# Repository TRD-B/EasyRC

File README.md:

# EasyRC - open-source RC platform

Description
---
EasyRC is an easy-to-build platform for creating your own remote-controlled vehicle. The platform includes CAD files for printing an affordable 1:16 scale car as well as a small remote control. Further, it includes the project and production files for the printed circuit boards that are needed to power these devices. Last but not least, it lists all required components in a bill of materials and comes with a complete instruction manual that shows how to print, solder, assemble, program, and adjust everything for running the car. The legacy folder contains data and information from previous revisions of the project.

The idea of this platform is to serve as a starting point for people who are interested in DIY hobby electronics as well as 3D printing, but were reluctant so far due to the initial burdens that are associated with the complexity of these topics. Hence, EasyRC offers a simple start for beginners, but due to its open-source character, it offers full freedom to tweak, redesign, and reprogram all parts of the project.

The 1:16 scale vehicle is designed for indoor use (for the sake of simplicity, it does not encompass suspension) and can be safely operated by kids (maximum speed is 10 km/h but can be set lower within the software). Hence, the project is also a great gift for kids who want to dive into engineering and programming topics, or start with driving a selfmade remote-controlled car and look behind the scenes once they're getting older.

The manual is available in English and German.

Specifications
---
Vehicle:
- Size: 282x125x95 mm³ (LxWxH)
- Scale: 1:16
- Weight: approx. 1 kg (including batteries)
- Microcontroller: ESP32-C3
- Wireless communication: 2.4 GHz (ESP-NOW protocol)
- Motor driver: Pololu DRV8876 (QFN)
- Drive motor: JGA25-370 Brushed DC motor with gearbox (12 V, 1000 U/min)
- Speed: max. 10 km/h
- Steering servo: MG90S metal-gear micro servo
- Power supply: 3x 18650 Li-Ion battery (11.1 V)
- Power consumption: approx. 0.8 W (idle); approx. 3-6 W (driving)

Remote control:
- Size: 80x40x41 mm³ (LxWxH)
- Weight: approx. 125 g (including battery)
- Microcontroller: ESP32-C3
- Wireless communication: 2.4 GHz (ESP-NOW protocol)
- Joystick: Alps 10k (Playstation 4 model)
- Power supply: 1x 18650 Li-Ion battery (3.7 V)
- Power consumption: approx. 0.5 W

Safety information:
---
- Voltage levels are 12 V or less (harmless for humans)
-	Battery connectors are reverse polarity protected
-	Low battery warnings are included
-	The motor automatically stops if the connection to the remote control is lost

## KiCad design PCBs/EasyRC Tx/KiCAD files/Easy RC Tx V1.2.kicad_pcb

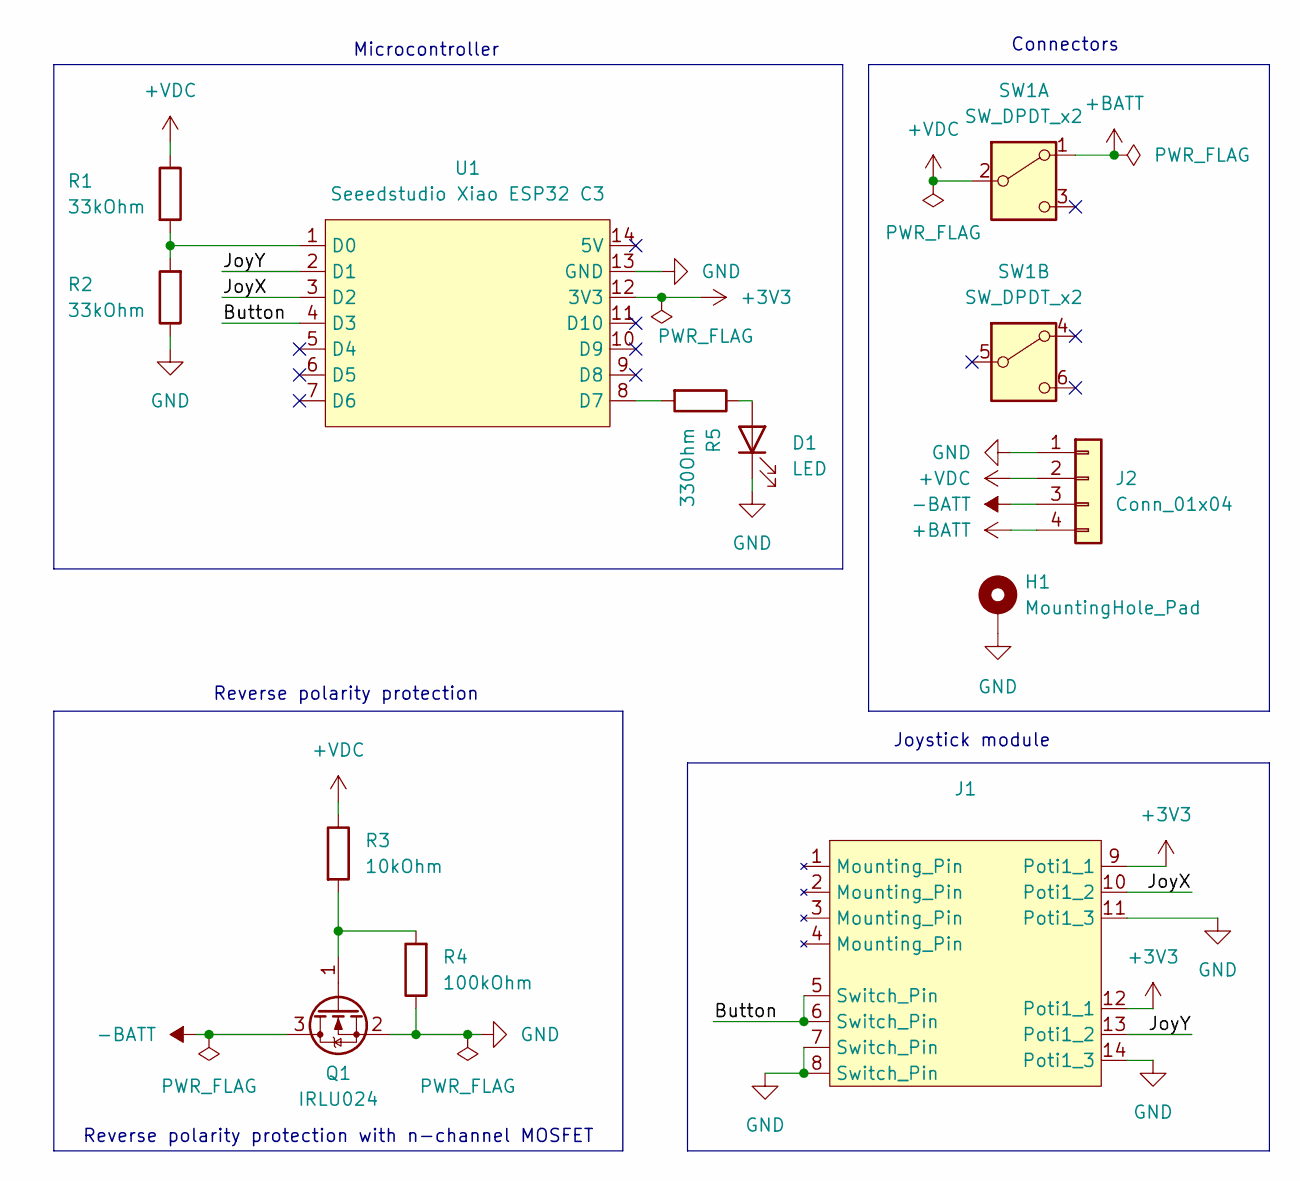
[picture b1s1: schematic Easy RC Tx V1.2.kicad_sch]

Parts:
D1: LED; LED_D5.0mm
H1: MountingHole_Pad; MountingHole_3.2mm_M3_DIN965_Pad_TopBottom
J1: PS5 Joystick
J2: Conn_01x04; PinHeader_1x04_P2.54mm_Horizontal
Q1: IRLU024; TO-251-3_Vertical
R1, R2: 33kOhm; R_Axial_DIN0207_L6.3mm_D2.5mm_P2.54mm_Vertical
R3: 10kOhm; R_Axial_DIN0207_L6.3mm_D2.5mm_P2.54mm_Vertical
R4: 100kOhm; R_Axial_DIN0207_L6.3mm_D2.5mm_P2.54mm_Vertical
R5: 330Ohm; R_Axial_DIN0207_L6.3mm_D2.5mm_P2.54mm_Vertical
SW1: SW_DPDT_x2; Wentronic S166 slide switch
U1: Seeedstudio Xiao ESP32 C3; Xiao ESP32C3

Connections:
+3V3: J1.9 (Poti1_1), J1.12 (Poti1_1), U1.12 (3V3)
+BATT: J2.4, SW1.1 (A)
+VDC: J2.2, R1.1, R3.1, SW1.2 (B)
-BATT: J2.3, Q1.3 (D)
/Button: J1.5 (Switch_Pin), J1.6 (Switch_Pin), U1.4 (D3)
/JoyX: J1.10 (Poti1_2), U1.3 (D2)
/JoyY: J1.13 (Poti1_2), U1.2 (D1)
GND: D1.1 (K), H1.1, J1.7 (Switch_Pin), J1.8 (Switch_Pin), J1.11 (Poti1_3), J1.14 (Poti1_3), J2.1, Q1.2 (S), R2.1, R4.1, U1.13 (GND)
unnamed: D1.2 (A), R5.1
unnamed: Q1.1 (G), R3.2, R4.2
unnamed: R1.2, R2.2, U1.1 (D0)
unnamed: R5.2, U1.8 (D7)

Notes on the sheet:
Reverse polarity protection
Joystick module
Connectors
Microcontroller
Reverse polarity protection with n-channel MOSFET

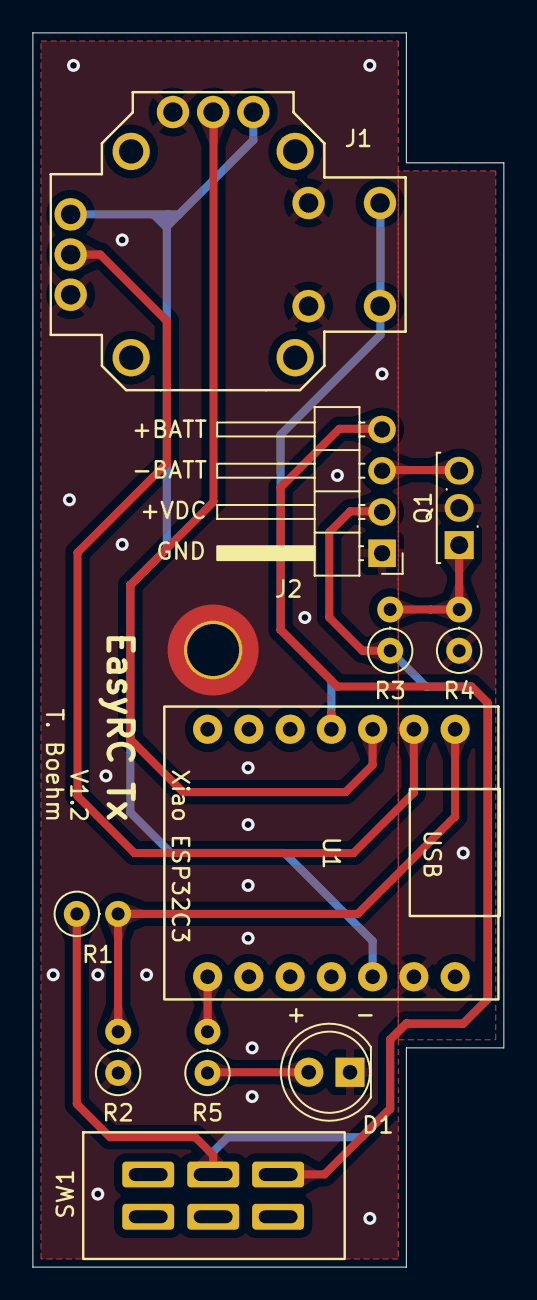
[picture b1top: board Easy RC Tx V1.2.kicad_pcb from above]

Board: 2 copper layers, 29.0 x 76.0 mm, 12 parts (0 on the bottom side), 12 nets.

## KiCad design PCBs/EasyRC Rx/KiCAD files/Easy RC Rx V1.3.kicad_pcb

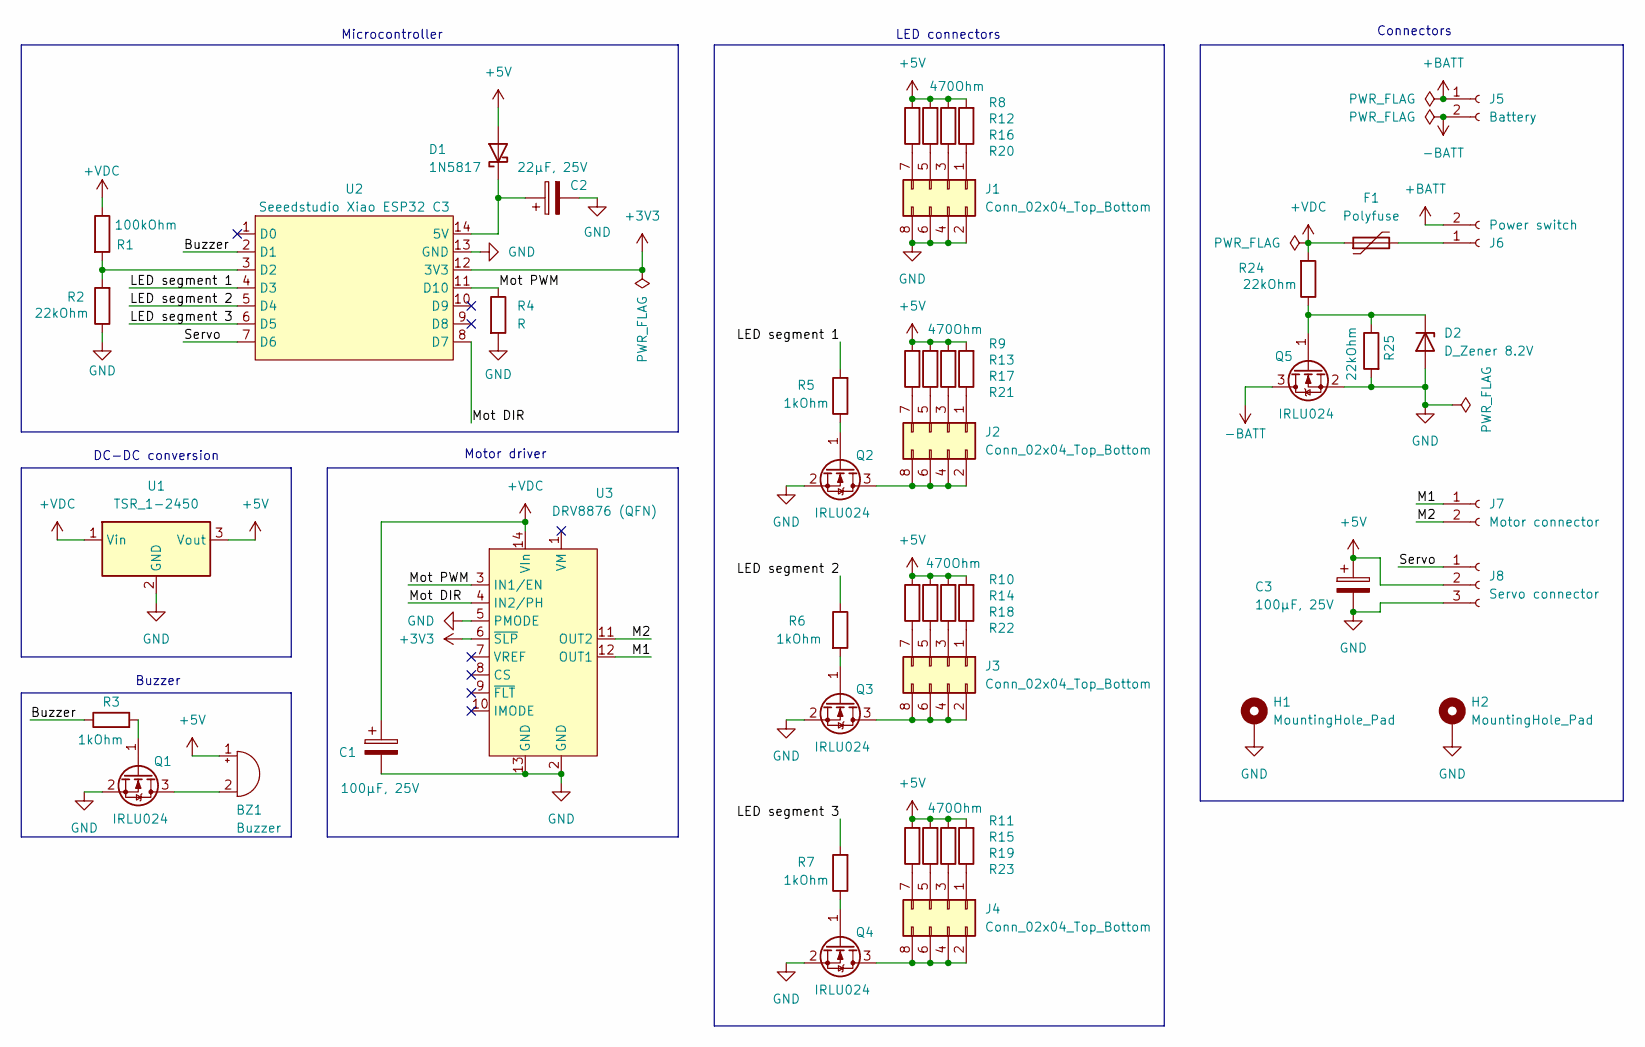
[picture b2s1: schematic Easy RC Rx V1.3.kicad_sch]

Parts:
BZ1: Buzzer; Buzzer 12mm 6.5mm spacing
C1, C3: 100µF, 25V; CP_Radial_D6.3mm_P2.50mm
C2: 22µF, 25V; CP_Radial_D5.0mm_P2.50mm
D1: 1N5817; D_DO-41_SOD81_P7.62mm_Horizontal
D2: D_Zener 8.2V; D_DO-41_SOD81_P7.62mm_Horizontal
F1: Polyfuse; ESKA FRG300-16F PTC Fuse
H1, H2: MountingHole_Pad; MountingHole_3.2mm_M3_DIN965_Pad_TopBottom
J1, J2, J3, J4: Conn_02x04_Top_Bottom; PinHeader_2x04_P2.54mm_Vertical
J5: Battery; PinHeader_1x02_P2.54mm_Vertical
J6: Power switch; PinHeader_1x02_P2.54mm_Vertical
J7: Motor connector; PinHeader_1x02_P2.54mm_Vertical
J8: Servo connector; PinHeader_1x03_P2.54mm_Vertical
Q1, Q2, Q3, Q4, Q5: IRLU024; TO-251-3_Vertical
R1: 100kOhm; R_Axial_DIN0207_L6.3mm_D2.5mm_P7.62mm_Horizontal
R2: 22kOhm; R_Axial_DIN0207_L6.3mm_D2.5mm_P7.62mm_Horizontal
R3, R5, R6, R7: 1kOhm; R_Axial_DIN0207_L6.3mm_D2.5mm_P2.54mm_Vertical
R4: R; R_Axial_DIN0207_L6.3mm_D2.5mm_P7.62mm_Horizontal
R8, R9, R10, R11, R12, R13, R14, R15, R16, R17, R18, R19, R20, R21, R22, R23: 470Ohm; R_Axial_DIN0207_L6.3mm_D2.5mm_P2.54mm_Vertical
R24, R25: 22kOhm; R_Axial_DIN0207_L6.3mm_D2.5mm_P2.54mm_Vertical
U1: TSR_1-2450; Converter_DCDC_TRACO_TSR-1_THT
U2: Seeedstudio Xiao ESP32 C3; Xiao ESP32C3
U3: DRV8876 (QFN); DRV8876(QFN)

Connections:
+3V3: U2.12 (3V3), U3.6 (~SLP)
+5V: BZ1.1 (+), C3.1, D1.2 (A), J8.2, R8.2, R9.2, R10.2, R11.2, R12.2, R13.2, R14.2, R15.2, R16.2, R17.2, R18.2, R19.2, R20.2, R21.2, R22.2, R23.2, U1.3 (Vout)
+BATT: J5.1, J6.2
+VDC: C1.1, F1.1, R1.1, R24.2, U1.1 (Vin), U3.14 (VIn)
-BATT: J5.2, Q5.3 (D)
/Buzzer: R3.1, U2.2 (D1)
/LED segment 1: R5.2, U2.4 (D3)
/LED segment 2: R6.1, U2.5 (D4)
/LED segment 3: R7.2, U2.6 (D5)
/M1: J7.1, U3.12 (OUT1)
/M2: J7.2, U3.11 (OUT2)
/Mot DIR: U2.8 (D7), U3.4 (IN2/PH)
/Mot PWM: R4.1, U2.11 (D10), U3.3 (IN1/EN)
/Servo: J8.1, U2.7 (D6)
GND: C1.2, C2.2, C3.2, D2.2 (A), H1.1, H2.1, J1.2, J1.4, J1.6, J1.8, J8.3, Q1.2 (S), Q2.2 (S), Q3.2 (S), Q4.2 (S), Q5.2 (S), R2.1, R4.2, R25.2, U1.2 (GND), U2.13 (GND), U3.2 (GND), U3.5 (PMODE), U3.13 (GND)
unnamed: BZ1.2 (-), Q1.3 (D)
unnamed: C2.1, D1.1 (K), U2.14 (5V)
unnamed: D2.1 (K), Q5.1 (G), R24.1, R25.1
unnamed: J1.1, R20.1
unnamed: J1.3, R16.1
unnamed: J1.5, R12.1
unnamed: J1.7, R8.1
unnamed: J2.1, R21.1
unnamed: J2.2, J2.4, J2.6, J2.8, Q2.3 (D)
unnamed: J2.3, R17.1
unnamed: J2.5, R13.1
unnamed: J2.7, R9.1
unnamed: J3.1, R22.1
unnamed: J3.2, J3.4, J3.6, J3.8, Q3.3 (D)
unnamed: J3.3, R18.1
unnamed: J3.5, R14.1
unnamed: J3.7, R10.1
unnamed: J4.1, R23.1
unnamed: J4.2, J4.4, J4.6, J4.8, Q4.3 (D)
unnamed: J4.3, R19.1
unnamed: J4.5, R15.1
unnamed: J4.7, R11.1
unnamed: F1.2, J6.1
unnamed: Q1.1 (G), R3.2
unnamed: Q2.1 (G), R5.1
unnamed: Q3.1 (G), R6.2
unnamed: Q4.1 (G), R7.1
unnamed: R1.2, R2.2, U2.3 (D2)

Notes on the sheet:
Buzzer
Microcontroller
LED connectors
DC-DC conversion
Connectors
Motor driver

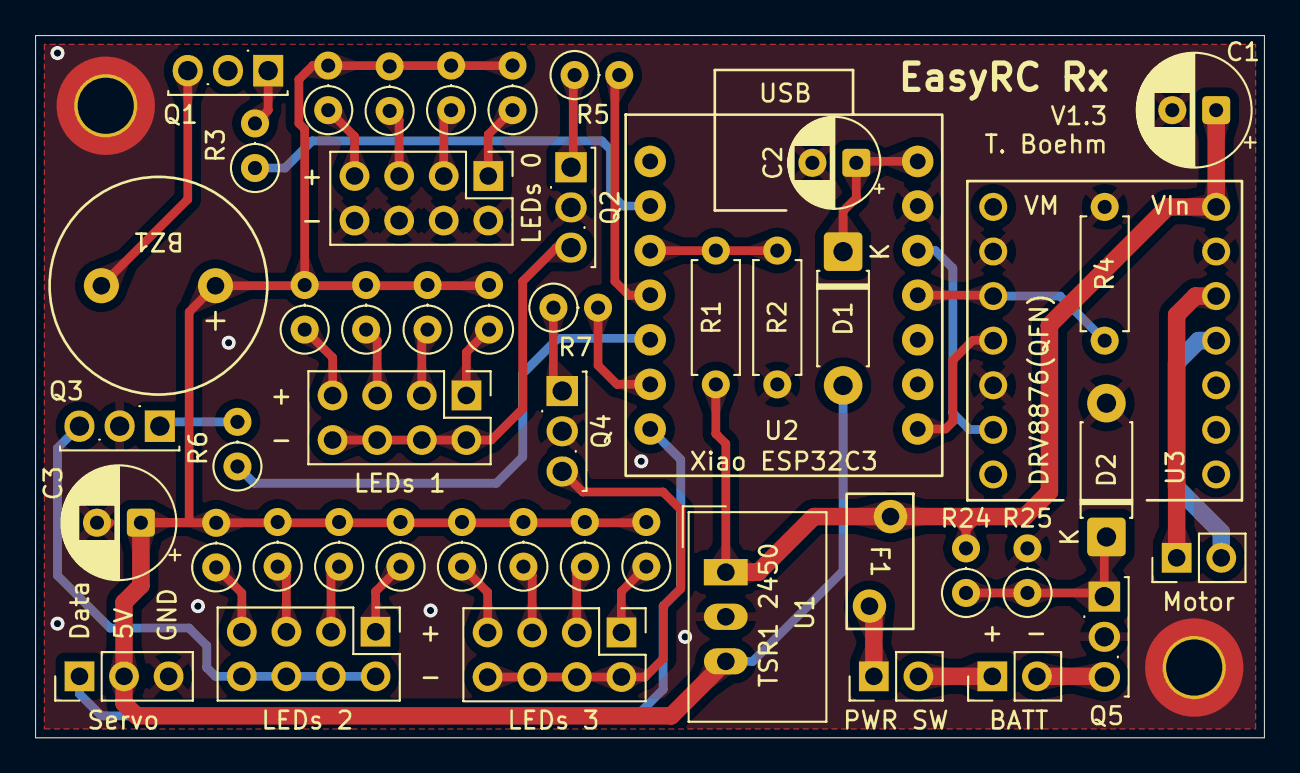
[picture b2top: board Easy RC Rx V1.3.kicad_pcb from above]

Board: 2 copper layers, 70.0 x 40.0 mm, 50 parts (0 on the bottom side), 43 nets.

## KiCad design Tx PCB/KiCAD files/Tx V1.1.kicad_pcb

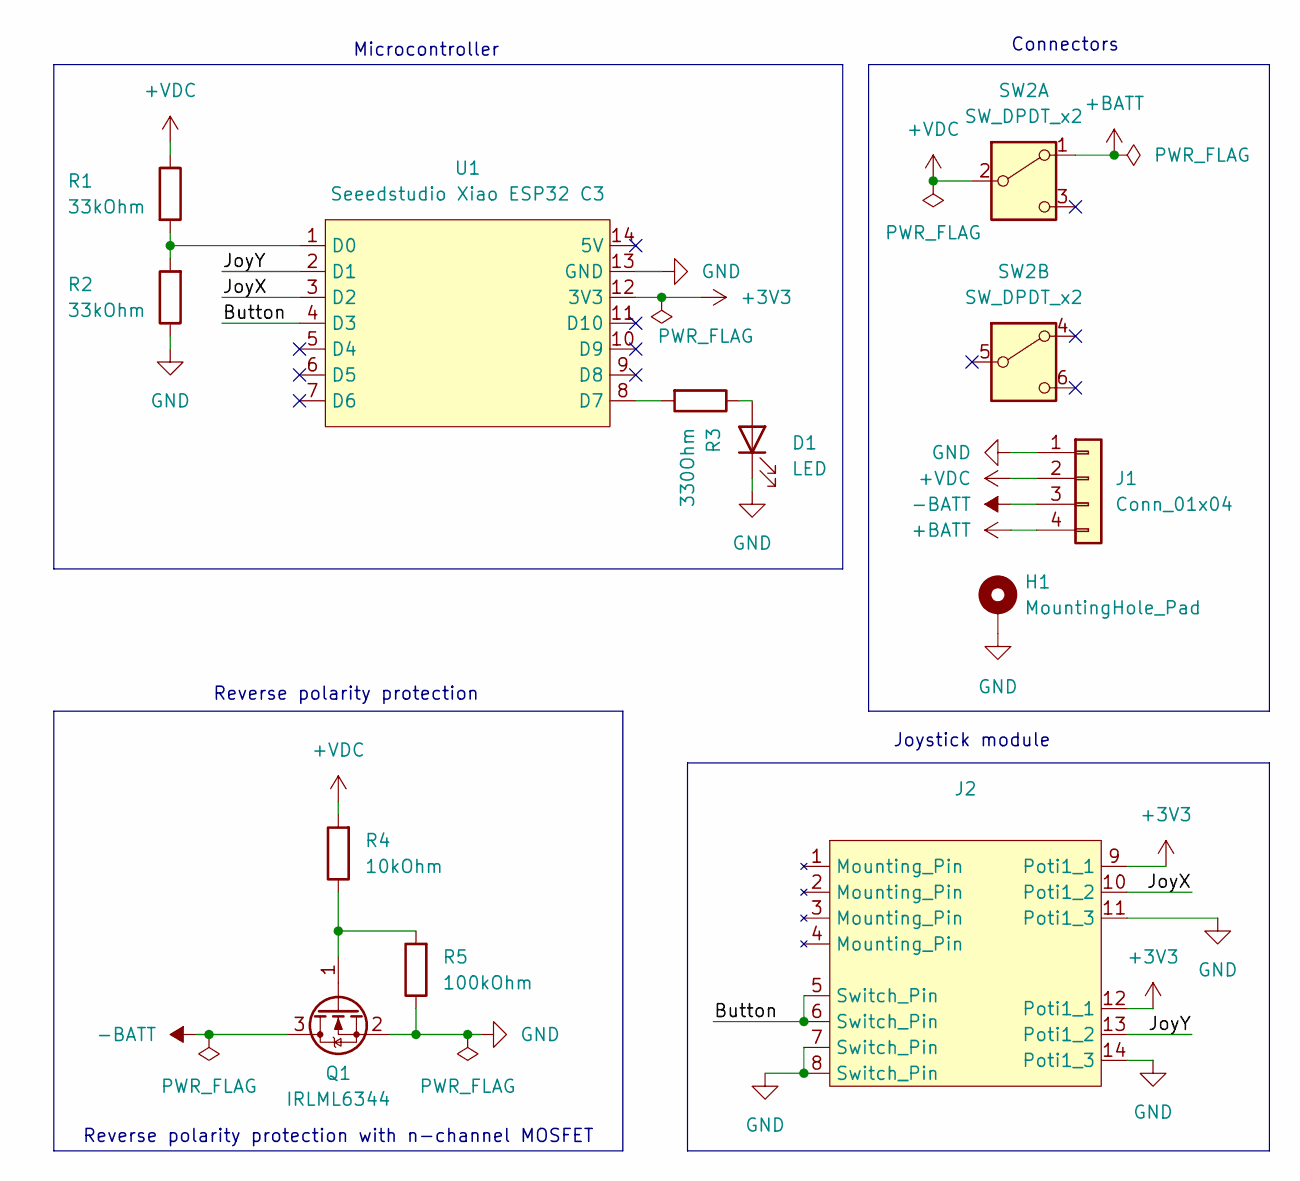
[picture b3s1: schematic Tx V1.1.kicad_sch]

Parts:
D1: LED; LED_D5.0mm
H1: MountingHole_Pad; MountingHole_3.2mm_M3_DIN965_Pad_TopBottom
J1: Conn_01x04; PinHeader_1x04_P2.54mm_Horizontal
J2: PS5 Joystick
Q1: IRLML6344; SOT-23
R1, R2: 33kOhm; R_0805_2012Metric_Pad1.20x1.40mm_HandSolder
R3: 330Ohm; R_0805_2012Metric_Pad1.20x1.40mm_HandSolder
R4: 10kOhm; R_0805_2012Metric_Pad1.20x1.40mm_HandSolder
R5: 100kOhm; R_0805_2012Metric_Pad1.20x1.40mm_HandSolder
SW2: SW_DPDT_x2; Wentronic S166 slide switch
U1: Seeedstudio Xiao ESP32 C3; Xiao ESP32C3

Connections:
+3V3: J2.9 (Poti1_1), J2.12 (Poti1_1), U1.12 (3V3)
+BATT: J1.4, SW2.1 (A)
+VDC: J1.2, R1.1, R4.2, SW2.2 (B)
-BATT: J1.3, Q1.3 (D)
/Button: J2.5 (Switch_Pin), J2.6 (Switch_Pin), U1.4 (D3)
/JoyX: J2.10 (Poti1_2), U1.3 (D2)
/JoyY: J2.13 (Poti1_2), U1.2 (D1)
GND: D1.1 (K), H1.1, J1.1, J2.7 (Switch_Pin), J2.8 (Switch_Pin), J2.11 (Poti1_3), J2.14 (Poti1_3), Q1.2 (S), R2.1, R5.1, U1.13 (GND)
unnamed: D1.2 (A), R3.1
unnamed: Q1.1 (G), R4.1, R5.2
unnamed: R1.2, R2.2, U1.1 (D0)
unnamed: R3.2, U1.8 (D7)

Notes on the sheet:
Reverse polarity protection
Joystick module
Connectors
Microcontroller
Reverse polarity protection with n-channel MOSFET

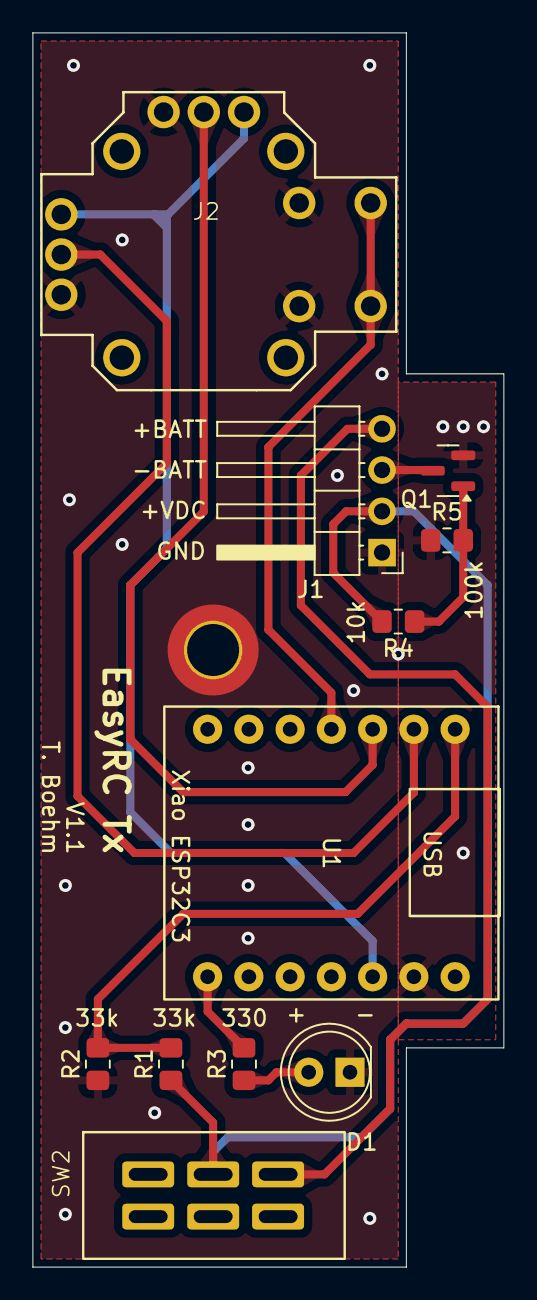
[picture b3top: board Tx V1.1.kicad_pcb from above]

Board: 2 copper layers, 29.0 x 76.0 mm, 12 parts (0 on the bottom side), 12 nets.

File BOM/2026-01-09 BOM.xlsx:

Component | Description | Amount needed | Pieces per unit | Required units | Costs per unit | Costs per piece | Scaled price | Total cost | Link
Motor | Brushed 370 with 1:10 gearbox | 1 | 1 | 1 | 8.49 | 8.49 | 8.49 | 8.49 | https://www.amazon.de/dp/B07ZKKN226?
Servo | MG90S metal gear micro servo | 1 | 1 | 1 | 4 | 4 | 4 | 4 | https://funduinoshop.com/elektronische-module/elektromotoren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
Battery holder | 3x18650 | 1 | 1 | 1 | 1.87 | 1.87 | 1.87 | 1.87 | https://funduinoshop.com/werkstatt/stromversorgung/batterief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
Battery holder | 1x18650 | 1 | 1 | 1 | 1.06 | 1.06 | 1.06 | 1.06 | https://funduinoshop.com/werkstatt/stromversorgung/batterief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
Battery | Lishen 18650 3.1 Ah | 4 | 10 | 1 | 26.5 | 2.65 | 10.6 | 26.5 | https://www.pollin.de/p/liion-akku-lishen-lr1865ss-3-6v-3-1a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
Microcontroller | Xiao ESP32-C3 | 2 | 1 | 2 | 5.9 | 5.9 | 11.8 | 11.8 | https://botland.de/wifi-und-bt-module-esp32/21859-seeed-xiao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
On/off switch | Marquardt 1801.1148 | 1 | 1 | 1 | 1.8 | 1.8 | 1.8 | 1.8 | https://www.reichelt.de/de/de/shop/produkt/wippschalter_ein_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
On/off switch | Miniature slide switch | 1 | 1 | 1 | 0.48 | 0.48 | 0.48 | 0.48 | https://www.reichelt.de/de/de/shop/produkt/schiebeschalter-m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
Fuse | PTC, 1.5A | 1 | 1 | 1 | 0.76 | 0.76 | 0.76 | 0.76 | https://www.reichelt.de/de/de/shop/produkt/ptc-sicherung_smd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
DC-DC converter | TSR1-2450E | 1 | 1 | 1 | 3.99 | 3.99 | 3.99 | 3.99 | https://www.reichelt.de/de/de/shop/produkt/dc_dc_converter_t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
Capacitor | Electrolytic, 100µF 25V 6.3mm pitch 2.5mm | 2 | 1 | 2 | 0.25 | 0.25 | 0.5 | 0.5 | https://www.reichelt.de/de/de/shop/produkt/elko_radial_100_u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
Buzzer | PB1220PE05Q | 1 | 1 | 1 | 0.5 | 0.5 | 0.5 | 0.5 | https://www.reichelt.de/de/de/shop/produkt/ac-signalgeber_85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
LED | 5 mm, white | 2 | 1 | 2 | 0.08 | 0.08 | 0.16 | 0.16 | https://www.reichelt.de/de/de/shop/produkt/led_5_mm_bedrahte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
LED | 5 mm, yellow | 4 | 1 | 4 | 0.08 | 0.08 | 0.32 | 0.32 | https://www.reichelt.de/de/de/shop/produkt/led_5_mm_bedrahte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
LED | 5 mm, red | 2 | 1 | 2 | 0.08 | 0.08 | 0.16 | 0.16 | https://www.reichelt.de/de/de/shop/produkt/led_5_mm_bedrahte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
LED | 5 mm, green | 1 | 1 | 1 | 0.08 | 0.08 | 0.08 | 0.08 | https://www.reichelt.de/de/de/shop/produkt/led_5_mm_bedrahte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
Motor driver | Pololu DRV8876 QFN | 1 | 1 | 1 | 6.5 | 6.5 | 6.5 | 6.5 | https://botland.de/motortreiber-module/21361-drv8876-qfn-ein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
MOSFET | IRLML6344 | 6 | 1 | 6 | 0.25 | 0.25 | 1.5 | 1.5 | https://www.reichelt.de/de/de/shop/produkt/mosfet_n-ch_30v_5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
Zener diode | CDIL SMD ZD 8.2 | 1 | 1 | 1 | 0.04 | 0.04 | 0.04 | 0.04 | https://www.reichelt.de/de/de/shop/produkt/zenerdiode_8_2_v_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
Capacitor | ceramic, 22µF 10V 1206 | 2 | 1 | 2 | 0.26 | 0.26 | 0.52 | 0.52 | https://www.reichelt.de/de/de/shop/produkt/smd-vielschichtko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
Capacitor | ceramic 100nF 50V 0805 | 1 | 1 | 1 | 0.03 | 0.03 | 0.03 | 0.03 | https://www.reichelt.de/de/de/shop/produkt/smd-kerko_0805_10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
Resistor | 330Ohm 0805 | 1 | 1 | 1 | 0.02 | 0.02 | 0.02 | 0.02 | https://www.reichelt.de/de/de/shop/produkt/smd-widerstand_08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
Resistor | 470Ohm 0805 | 16 | 1 | 16 | 0.02 | 0.02 | 0.32 | 0.32 | https://www.reichelt.de/de/de/shop/produkt/smd-widerstand_08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
Resistor | 1kOhm 0805 | 4 | 1 | 1 | 0.02 | 0.02 | 0.08 | 0.02 | https://www.reichelt.de/de/de/shop/produkt/smd-widerstand_08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
Resistor | 22kOhm 0805 | 3 | 1 | 1 | 0.02 | 0.02 | 0.06 | 0.02 | https://www.reichelt.de/de/de/shop/produkt/smd-widerstand_08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
Resistor | 10kOhm 0805 | 1 | 1 | 1 | 0.02 | 0.02 | 0.02 | 0.02 | https://www.reichelt.de/de/de/shop/produkt/smd-widerstand_08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
Resistor | 33kOhm 0805 | 2 | 1 | 2 | 0.02 | 0.02 | 0.04 | 0.04 | https://www.reichelt.de/de/de/shop/produkt/smd-widerstand_08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
Resistor | 100kOhm 0805 | 2 | 1 | 1 | 0.02 | 0.02 | 0.04 | 0.02 | https://www.reichelt.de/de/de/shop/produkt/smd-widerstand_08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
Joystick | ALPS PS4 Joystick | 1 | 1 | 1 | 2.9 | 2.9 | 2.9 | 2.9 | https://www.retroretter.de/products/as_ps4_white_alps_10k?sr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
Pin header | W+P 10-pin angled | 1 | 2 | 1 | 0.36 | 0.18 | 0.18 | 0.36 | https://www.reichelt.de/de/de/shop/produkt/stiftleiste_rm_2_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
Socket strip | mpe 7-pin | 4 | 1 | 6 | 0.31 | 0.31 | 1.24 | 1.8599999999999999 | https://www.reichelt.de/de/de/shop/produkt/buchsenleisten_2_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
Socket strip | 10-pin (5 mm height) | 2 | 1 | 1 | 0.75 | 0.75 | 1.5 | 0.75 | https://www.reichelt.de/de/de/shop/produkt/10pol_buchsenleis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
Pin header | mpe 1x20-pin | 5 | 5 | 1 | 0.35 | 6.9999999999999993E-2 | 0.35 | 0.35 | https://www.reichelt.de/de/de/shop/produkt/stiftleisten_2_54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
Pin header | mpe 2x20-pin | 4 | 4 | 1 | 0.69 | 0.17249999999999999 | 0.69 | 0.69 | https://www.reichelt.de/de/de/shop/produkt/stiftleisten_2_54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
Jumper | 2.54 mm Jumper | 1 | 1 | 1 | 0.02 | 0.02 | 0.02 | 0.02 | https://www.reichelt.de/de/de/shop/produkt/kurzschlussbrueck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
Crimp set | Dupont 610 parts | 15 | 100 | 1 | 9.75 | 9.7500000000000003E-2 | 1.4625000000000001 | 9.75 | https://www.reichelt.de/de/de/shop/produkt/entwicklerboards_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
Wire | 0.25 mm², black, 25m | 4 | 25 | 1 | 4.7 | 0.188 | 0.752 | 4.7 | https://www.pollin.de/p/rautronic-schaltlitze-liyv-0-25-mm2-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
Wire | 0.25 mm², red, 25m | 4 | 25 | 1 | 4.7 | 0.188 | 0.752 | 4.7 | https://www.pollin.de/p/rautronic-schaltlitze-liyv-0-25-mm2-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
Ball bearing | 608ZZ 8x22x7 | 4 | 50 | 1 | 9.99 | 0.19980000000000001 | 0.79920000000000002 | 9.99 | https://www.amazon.de/Rillenkugellager-Carbonstahl-Pr%C3%A4z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
Ball bearing | 605ZZ 5x14x5 | 4 | 30 | 1 | 8.99 | 0.29966666666666669 | 1.1986666666666668 | 8.99 | https://www.amazon.de/QUARKZMAN-Rillenkugel-Bohrung-Karbonst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
Ball bearing | 6802ZZ 15x24x5 | 2 | 10 | 1 | 6.72 | 0.67199999999999993 | 1.3439999999999999 | 6.72 | https://www.motedis.com/de/Rillenkugellager-6802-2Z-15x24x5
Filament | PETG, black | 400 | 1000 | 1 | 32.99 | 3.2990000000000005E-2 | 13.196000000000002 | 32.99 | https://www.prusa3d.com/product/prusament-petg-jet-black-1kg/
Filament | PETG, red | 250 | 1000 | 1 | 32.99 | 3.2990000000000005E-2 | 8.2475000000000005 | 32.99 | https://www.prusa3d.com/product/prusament-petg-lipstick-red-1kg/
Filament | TPU, 82A | 35 | 500 | 1 | 32.99 | 6.5980000000000011E-2 | 2.3093000000000004 | 32.99 | https://www.3djake.de/recreus/filaflex-black
Screw | M3x8 | 29 | 100 | 1 | 3.58 | 3.5799999999999998E-2 | 1.0382 | 3.58 | https://shop.der-schraubenladen.de/DIN-912-ISO-4762-Zylinder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
Screw | M3x10 countersunk | 3 | 1000 | 1 | 19.350000000000001 | 1.9350000000000003E-2 | 5.8050000000000004E-2 | 19.350000000000001 | https://shop.der-schraubenladen.de/DIN-7991-ISO-10642-Senksc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
Screw | M3x12 | 4 | 100 | 1 | 3.9 | 3.9E-2 | 0.156 | 3.9 | https://shop.der-schraubenladen.de/DIN-912-ISO-4762-Zylinder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
Screw | M3x16 | 7 | 100 | 1 | 4.37 | 4.3700000000000003E-2 | 0.30590000000000001 | 4.37 | https://shop.der-schraubenladen.de/DIN-912-ISO-4762-Zylinder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
Screw | M3x20 | 6 | 100 | 1 | 5.54 | 5.5399999999999998E-2 | 0.33239999999999997 | 5.54 | https://shop.der-schraubenladen.de/DIN-912-ISO-4762-Zylinder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
Screw | M3x22 | 2 | 100 | 1 | 6 | 0.06 | 0.12 | 6 | https://shop.der-schraubenladen.de/DIN-912-ISO-4762-Zylinder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
Screw | M3x30 | 17 | 100 | 1 | 7.57 | 7.5700000000000003E-2 | 1.2869000000000002 | 7.57 | https://shop.der-schraubenladen.de/DIN-912-ISO-4762-Zylinder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
Screw | M3x35 | 2 | 100 | 1 | 8.66 | 8.6599999999999996E-2 | 0.17319999999999999 | 8.66 | https://shop.der-schraubenladen.de/DIN-912-ISO-4762-Zylinder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
Screw | M3x40 | 2 | 100 | 1 | 9.69 | 9.69E-2 | 0.1938 | 9.69 | https://shop.der-schraubenladen.de/DIN-912-ISO-4762-Zylinder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
Hex nut | M3 | 64 | 500 | 1 | 10.76 | 2.1520000000000001E-2 | 1.3772800000000001 | 10.76 | https://shop.der-schraubenladen.de/DIN-934-ISO-4032-Sechskan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
PCB | JLCPCB | 1 | 5 | 1 | 8 | 1.6 | 1.6 | 8 | https://jlcpcb.com/
PCB | JLCPCB | 1 | 5 | 1 | 8 | 1.6 | 1.6 | 8 | https://jlcpcb.com/
 |  |  |  |  |  |  | Scaled | Prototype
Total costs |  |  |  |  |  |  | 100.92289666666665 | 317.69

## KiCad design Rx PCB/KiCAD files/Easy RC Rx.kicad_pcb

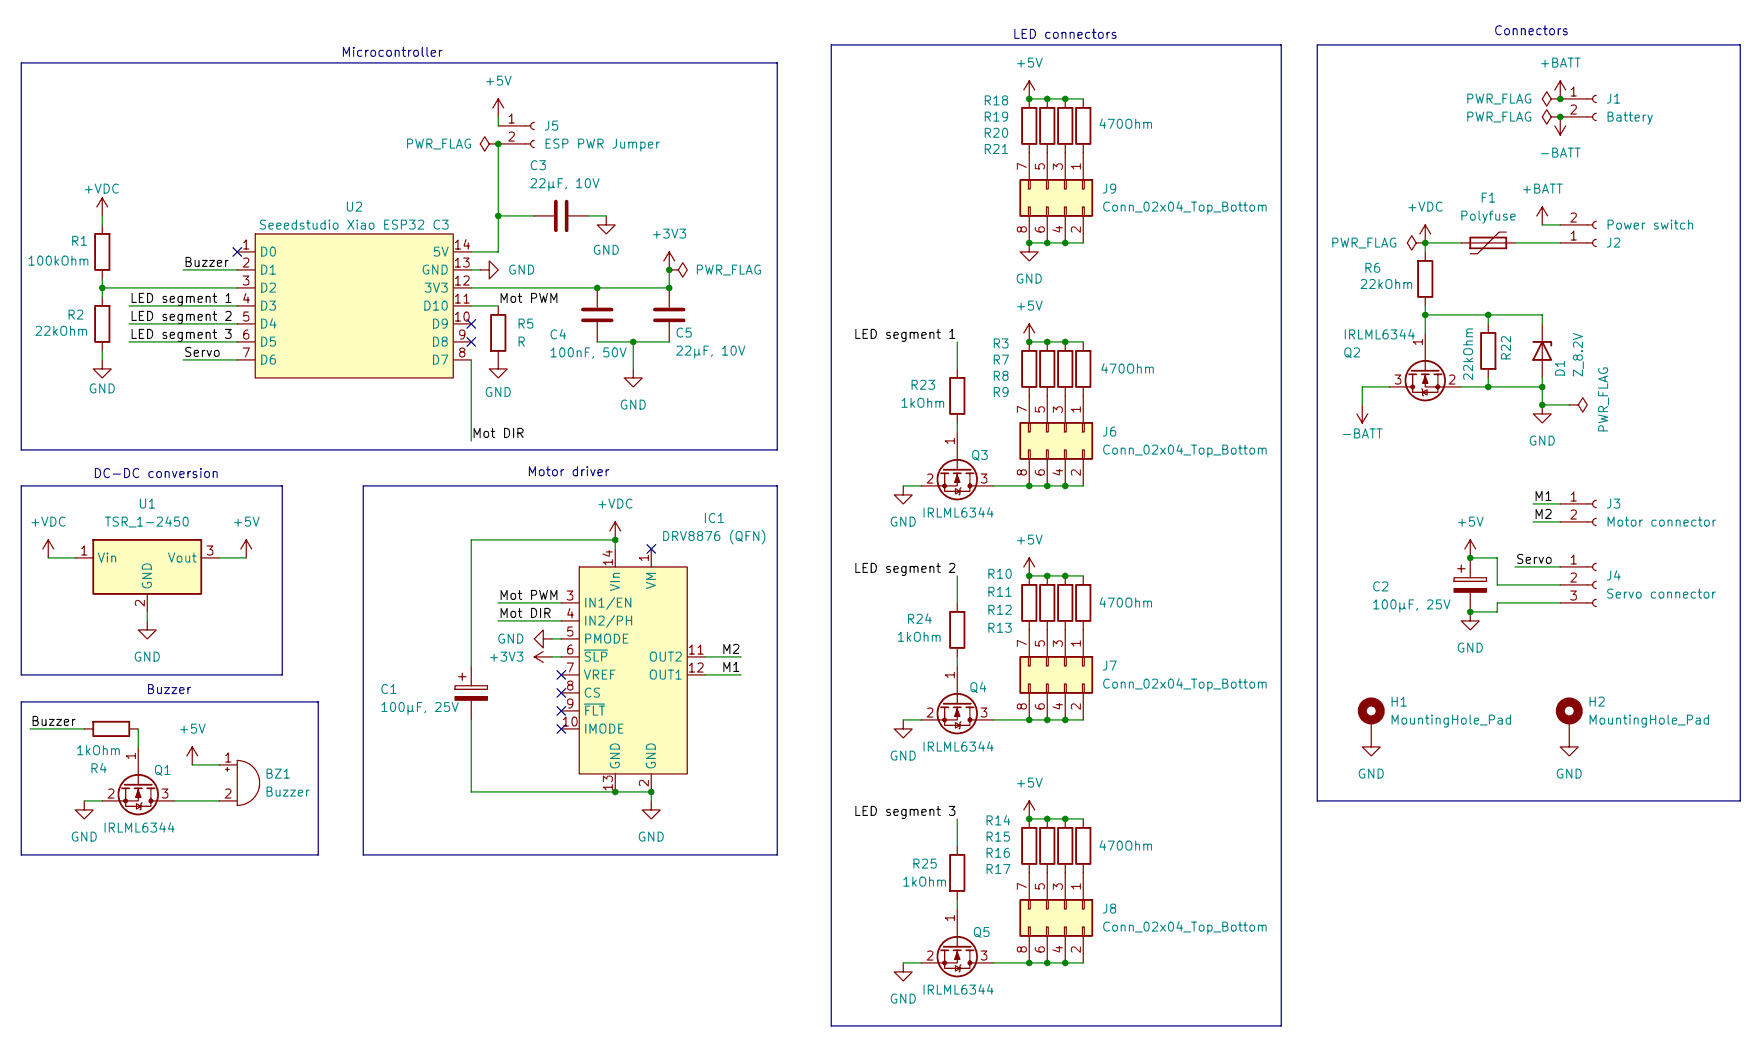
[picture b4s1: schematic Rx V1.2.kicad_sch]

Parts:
BZ1: Buzzer; Buzzer 12mm 6.5mm spacing
C1, C2: 100µF, 25V; CP_Radial_D6.3mm_P2.50mm
C3, C5: 22µF, 10V; C_1206_3216Metric_Pad1.33x1.80mm_HandSolder
C4: 100nF, 50V; C_0805_2012Metric_Pad1.18x1.45mm_HandSolder
D1: Z_8.2V; SOT-23_Handsoldering
F1: Polyfuse; Fuse_1812_4532Metric_Pad1.30x3.40mm_HandSolder
H1, H2: MountingHole_Pad; MountingHole_3.2mm_M3_DIN965_Pad_TopBottom
IC1: DRV8876 (QFN); DRV8876(QFN)
J1: Battery; PinHeader_1x02_P2.54mm_Vertical
J2: Power switch; PinHeader_1x02_P2.54mm_Vertical
J3: Motor connector; PinHeader_1x02_P2.54mm_Vertical
J4: Servo connector; PinHeader_1x03_P2.54mm_Vertical
J5: ESP PWR Jumper; PinHeader_1x02_P2.54mm_Vertical
J6, J7, J8, J9: Conn_02x04_Top_Bottom; PinHeader_2x04_P2.54mm_Vertical
Q1, Q2, Q3, Q4, Q5: IRLML6344; SOT-23
R1: 100kOhm; R_0805_2012Metric_Pad1.20x1.40mm_HandSolder
R2, R6, R22: 22kOhm; R_0805_2012Metric_Pad1.20x1.40mm_HandSolder
R3, R7, R8, R9, R10, R11, R12, R13, R14, R15, R16, R17, R18, R19, R20, R21: 470Ohm; R_0805_2012Metric_Pad1.20x1.40mm_HandSolder
R4, R23, R24, R25: 1kOhm; R_0805_2012Metric_Pad1.20x1.40mm_HandSolder
R5: R; R_0805_2012Metric_Pad1.20x1.40mm_HandSolder
U1: TSR_1-2450; Converter_DCDC_TRACO_TSR-1_THT
U2: Seeedstudio Xiao ESP32 C3; Xiao ESP32C3

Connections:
+3V3: C4.1, C5.1, IC1.6 (~SLP), U2.12 (3V3)
+5V: BZ1.1 (+), C2.1, J4.2, J5.1, R3.2, R7.2, R8.2, R9.2, R10.2, R11.2, R12.2, R13.2, R14.2, R15.2, R16.2, R17.2, R18.2, R19.2, R20.2, R21.2, U1.3 (Vout)
+BATT: J1.1, J2.2
+VDC: C1.1, F1.1, IC1.14 (VIn), R1.2, R6.2, U1.1 (Vin)
-BATT: J1.2, Q2.3 (D)
/Buzzer: R4.2, U2.2 (D1)
/LED segment 1: R23.2, U2.4 (D3)
/LED segment 2: R24.2, U2.5 (D4)
/LED segment 3: R25.1, U2.6 (D5)
/M1: IC1.12 (OUT1), J3.1
/M2: IC1.11 (OUT2), J3.2
/Mot DIR: IC1.4 (IN2/PH), U2.8 (D7)
/Mot PWM: IC1.3 (IN1/EN), R5.1, U2.11 (D10)
/Servo: J4.1, U2.7 (D6)
GND: C1.2, C2.2, C3.2, C4.2, C5.2, D1.1 (A), H1.1, H2.1, IC1.2 (GND), IC1.5 (PMODE), IC1.13 (GND), J4.3, J9.2, J9.4, J9.6, J9.8, Q1.2 (S), Q2.2 (S), Q3.2 (S), Q4.2 (S), Q5.2 (S), R2.1, R5.2, R22.2, U1.2 (GND), U2.13 (GND)
unnamed: BZ1.2 (-), Q1.3 (D)
unnamed: D1.3 (K), Q2.1 (G), R6.1, R22.1
unnamed: F1.2, J2.1
unnamed: C3.1, J5.2, U2.14 (5V)
unnamed: J6.1, R9.1
unnamed: J6.2, J6.4, J6.6, J6.8, Q3.3 (D)
unnamed: J6.3, R8.1
unnamed: J6.5, R7.1
unnamed: J6.7, R3.1
unnamed: J7.1, R13.1
unnamed: J7.2, J7.4, J7.6, J7.8, Q4.3 (D)
unnamed: J7.3, R12.1
unnamed: J7.5, R11.1
unnamed: J7.7, R10.1
unnamed: J8.1, R17.1
unnamed: J8.2, J8.4, J8.6, J8.8, Q5.3 (D)
unnamed: J8.3, R16.1
unnamed: J8.5, R15.1
unnamed: J8.7, R14.1
unnamed: J9.1, R21.1
unnamed: J9.3, R20.1
unnamed: J9.5, R19.1
unnamed: J9.7, R18.1
unnamed: Q1.1 (G), R4.1
unnamed: Q3.1 (G), R23.1
unnamed: Q4.1 (G), R24.1
unnamed: Q5.1 (G), R25.2
unnamed: R1.1, R2.2, U2.3 (D2)

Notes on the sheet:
Buzzer
Microcontroller
LED connectors
DC-DC conversion
Connectors
Motor driver

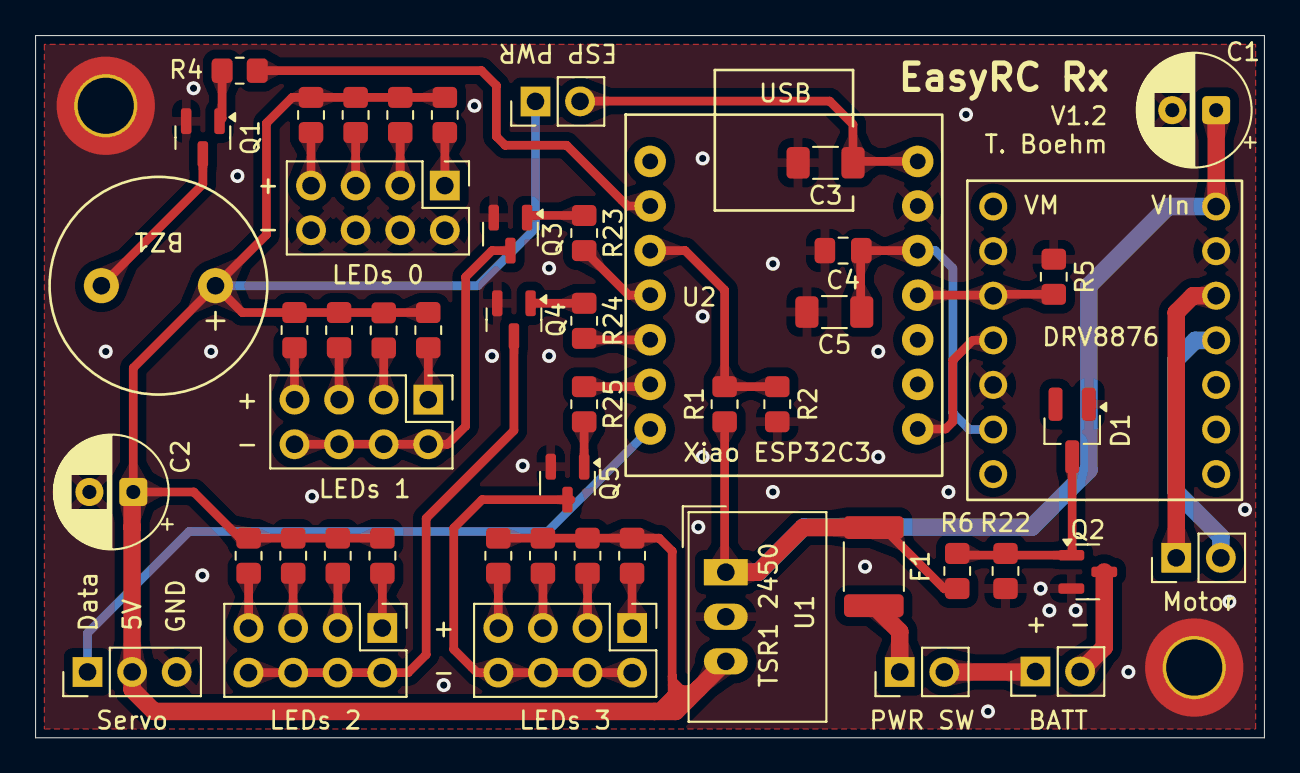
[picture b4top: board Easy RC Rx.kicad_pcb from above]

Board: 2 copper layers, 70.0 x 40.0 mm, 52 parts (0 on the bottom side), 43 nets.

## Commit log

2025-11-21 Create abc
2025-11-21 Create tobedone
2025-11-24 Delete Manual/German/Betriebsanleitung_V1.0.pdf
    Replaced by newer version
2026-01-02 Rename Easy RC car.7z to CAD files/Assembly/Easy RC car.7z
2026-01-02 Rename Easy RC Rx V1.2.zip to Rx PCB/Gerber files/Rx V1.2.zip
2026-01-02 Rename Easy RC Rx.kicad_pro to Rx V1.2.kicad_pro
2026-01-02 Rename Tx V1.1.zip to Tx PCB/Gerber files/Tx V1.1.zip
2026-01-02 Rename Tx V1.1.kicad_pro to Tx V1.1.kicad_pro
2026-01-09 Create temp
2026-01-09 Rename Rx PCB/Gerber files/Rx V1.2.zip to PCBs/EasyRC Rx/Gerber files/Rx V1.2.zip
2026-01-09 Rename Rx V1.2.kicad_pro to Rx V1.2.kicad_pro
2026-01-09 Rename EasyRC Rx/KiCAD files/Rx V1.2.kicad_pro to PCBs/EasyRC Rx/KiCAD files/Rx V1.2.kicad_pro
2026-01-09 Rename Tx PCB/Gerber files/Tx V1.1.zip to PCBs/EasyRC Tx/Gerber files/Tx V1.1.zip
2026-01-09 Rename Tx PCB/KiCAD files/Tx V1.1.kicad_pro to PCBs/EasyRC Tx/KiCAD files/Tx V1.1.kicad_pro
2026-01-09 Update LICENSE
2026-01-09 Rename 2026-01-09 BOM.xlsx to BOM/2026-01-09 BOM.xlsx
2026-04-11 Create tmp
2026-04-11 Rename BOM/2026-01-09 BOM.xlsx to Legacy/BOM/2026-01-09 BOM.xlsx
2026-04-11 Rename 2026-04-11 BOM.xlsx to BOM/2026-04-11 BOM.xlsx
2026-04-11 Rename CAD files/Assembly/Easy RC car.7z to Legacy/CAD files/Assembly/Easy RC car.7z
2026-04-11 Rename CAD files/Assembly/Easy RC remote control.step to Legacy/CAD files/Assembly/Easy RC remote control.step
2026-04-11 Rename CAD files/Car/10teeth crown gear.step to Legacy/CAD files/Car/10teeth crown gear.step
2026-04-11 Rename CAD files/Car/15teeth crown gear.step to Legacy/CAD files/Car/15teeth crown gear.step
2026-04-11 Rename CAD files/Car/16 teeth bearing mount.step to Legacy/CAD files/Car/16 teeth bearing mount.step
2026-04-11 Rename CAD files/Car/16 teeth gear.step to Legacy/CAD files/Car/16 teeth gear.step
2026-04-11 Rename CAD files/Car/24teeth gear.step to Legacy/CAD files/Car/24teeth gear.step
2026-04-11 Rename CAD files/Car/25teeth gear.step to Legacy/CAD files/Car/25teeth gear.step
2026-04-11 Rename CAD files/Car/Battery lid.step to Legacy/CAD files/Car/Battery lid.step
2026-04-11 Rename CAD files/Car/Chassis bottom.step to Legacy/CAD files/Car/Chassis bottom.step
2026-04-11 Rename CAD files/Car/Chassis securing bracket.step to Legacy/CAD files/Car/Chassis securing bracket.step
2026-04-11 Rename CAD files/Car/Chassis top.step to Legacy/CAD files/Car/Chassis top.step
2026-04-11 Rename CAD files/Car/Differential case.step to Legacy/CAD files/Car/Differential case.step
2026-04-11 Rename CAD files/Car/Differential spacer ring.step to Legacy/CAD files/Car/Differential spacer ring.step
2026-04-11 Rename CAD files/Car/Differential spacer.step to Legacy/CAD files/Car/Differential spacer.step
2026-04-11 Rename CAD files/Car/Front LED insert.step to Legacy/CAD files/Car/Front LED insert.step
2026-04-11 Rename CAD files/Car/Front body.step to Legacy/CAD files/Car/Front body.step
2026-04-11 Rename CAD files/Car/Front bumper.step to Legacy/CAD files/Car/Front bumper.step
2026-04-11 Rename CAD files/Car/Front light clamp.step to Legacy/CAD files/Car/Front light clamp.step
2026-04-11 Rename CAD files/Car/Front rim locking ring.step to Legacy/CAD files/Car/Front rim locking ring.step
2026-04-11 Rename CAD files/Car/Front rim spacer.step to Legacy/CAD files/Car/Front rim spacer.step
2026-04-11 Rename CAD files/Car/Front rim.step to Legacy/CAD files/Car/Front rim.step
2026-04-11 Rename CAD files/Car/Front wheel mount spacer.step to Legacy/CAD files/Car/Front wheel mount spacer.step
2026-04-11 Rename CAD files/Car/Front window.step to Legacy/CAD files/Car/Front window.step
2026-04-11 Rename CAD files/Car/Left front wheel mount.step to Legacy/CAD files/Car/Left front wheel mount.step
2026-04-11 Rename CAD files/Car/Left front window.step to Legacy/CAD files/Car/Left front window.step
2026-04-11 Rename CAD files/Car/Left rear LED insert.step to Legacy/CAD files/Car/Left rear LED insert.step
2026-04-11 Rename CAD files/Car/Left rear axle TPU.step to Legacy/CAD files/Car/Left rear axle TPU.step
2026-04-11 Rename CAD files/Car/Left rear window.step to Legacy/CAD files/Car/Left rear window.step
2026-04-11 Rename CAD files/Car/Rear body.step to Legacy/CAD files/Car/Rear body.step
2026-04-11 Rename CAD files/Car/Rear bumper.step to Legacy/CAD files/Car/Rear bumper.step
2026-04-11 Rename CAD files/Car/Rear light clamp.step to Legacy/CAD files/Car/Rear light clamp.step
2026-04-11 Rename CAD files/Car/Rear rim spacer.step to Legacy/CAD files/Car/Rear rim spacer.step
2026-04-11 Rename CAD files/Car/Rear rim.step to Legacy/CAD files/Car/Rear rim.step
2026-04-11 Rename CAD files/Car/Rear window.step to Legacy/CAD files/Car/Rear window.step
2026-04-11 Rename CAD files/Car/Rear wing holder.step to Legacy/CAD files/Car/Rear wing holder.step
2026-04-11 Rename CAD files/Car/Rear wing.step to Legacy/CAD files/Car/Rear wing.step
2026-04-11 Rename CAD files/Car/Right front wheel mount.step to Legacy/CAD files/Car/Right front wheel mount.step
2026-04-11 Rename CAD files/Car/Right front window.step to Legacy/CAD files/Car/Right front window.step
2026-04-11 Rename CAD files/Car/Right rear LED insert.step to Legacy/CAD files/Car/Right rear LED insert.step
2026-04-11 Rename CAD files/Car/Right rear axle TPU.step to Legacy/CAD files/Car/Right rear axle TPU.step
2026-04-11 Rename CAD files/Car/Right rear window.step to Legacy/CAD files/Car/Right rear window.step
2026-04-11 Rename CAD files/Car/Servo horn attachment large TPU.step to Legacy/CAD files/Car/Servo horn attachment large TPU.step
2026-04-11 Rename CAD files/Car/Servo horn attachment small TPU.step to Legacy/CAD files/Car/Servo horn attachment small TPU.step
2026-04-11 Rename CAD files/Car/Steering linkage connector.step to Legacy/CAD files/Car/Steering linkage connector.step
2026-04-11 Rename CAD files/Car/Steering linkage.step to Legacy/CAD files/Car/Steering linkage.step
2026-04-11 Rename CAD files/Car/Tire TPU.step to Legacy/CAD files/Car/Tire TPU.step
2026-04-11 Rename CAD files/Car/Window holder.step to Legacy/CAD files/Car/Window holder.step
2026-04-11 Rename CAD files/Remote control/Remote control battery cover.step to Legacy/CAD files/Remote control/Remote control battery cover.step
2026-04-11 Rename CAD files/Remote control/Remote control bottom.step to Legacy/CAD files/Remote control/Remote control bottom.step
2026-04-11 Rename CAD files/Remote control/Remote control joystick extension.step to Legacy/CAD files/Remote control/Remote control joystick extension.step
2026-04-11 Rename CAD files/Remote control/Remote control lower intermediate frame.step to Legacy/CAD files/Remote control/Remote control lower intermediate frame.step
2026-04-11 Rename CAD files/Remote control/Remote control top.step to Legacy/CAD files/Remote control/Remote control top.step
2026-04-11 Rename CAD files/Remote control/Remote control upper intermediate frame.step to Legacy/CAD files/Remote control/Remote control upper intermediate frame.step
2026-04-11 Rename Manual/English/Manual_V1.2.pdf to Legacy/Manual/English/Manual_V1.2.pdf
2026-04-11 Rename Manual/German/Betriebsanleitung_V1.1.pdf to Legacy/Manual/German/Betriebsanleitung_V1.1.pdf
2026-04-11 Rename PCBs/EasyRC Rx/KiCAD files/Rx V1.2.kicad_pcb to Legacy/PCBs/EasyRC Rx/KiCAD files/Rx V1.2.kicad_pcb
2026-04-11 Rename PCBs/EasyRC Rx/KiCAD files/Rx V1.2.kicad_pro to Legacy/PCBs/EasyRC Rx/KiCAD files/Rx V1.2.kicad_pro
2026-04-11 Rename PCBs/EasyRC Rx/KiCAD files/Rx V1.2.kicad_sch to Legacy/PCBs/EasyRC Rx/KiCAD files/Rx V1.2.kicad_sch
2026-04-11 Rename PCBs/EasyRC Tx/KiCAD files/Tx V1.1.kicad_pcb to Legacy/PCBs/EasyRC Tx/KiCAD files/Tx V1.1.kicad_pcb
2026-04-11 Rename PCBs/EasyRC Tx/KiCAD files/Tx V1.1.kicad_pro to Legacy/PCBs/EasyRC Tx/KiCAD files/Tx V1.1.kicad_pro
2026-04-11 Rename PCBs/EasyRC Tx/KiCAD files/Tx V1.1.kicad_sch to Legacy/PCBs/EasyRC Tx/KiCAD files/Tx V1.1.kicad_sch
2026-04-11 Rename PCBs/EasyRC Tx/Gerber files/Tx V1.1.zip to Legacy/PCBs/EasyRC Tx/Gerber files/Tx V1.1.zip
2026-04-11 Rename PCBs/EasyRC Rx/Gerber files/Easy RC Rx V1.2.zip to Legacy/PCBs/EasyRC Rx/Gerber files/Easy RC Rx V1.2.zip
